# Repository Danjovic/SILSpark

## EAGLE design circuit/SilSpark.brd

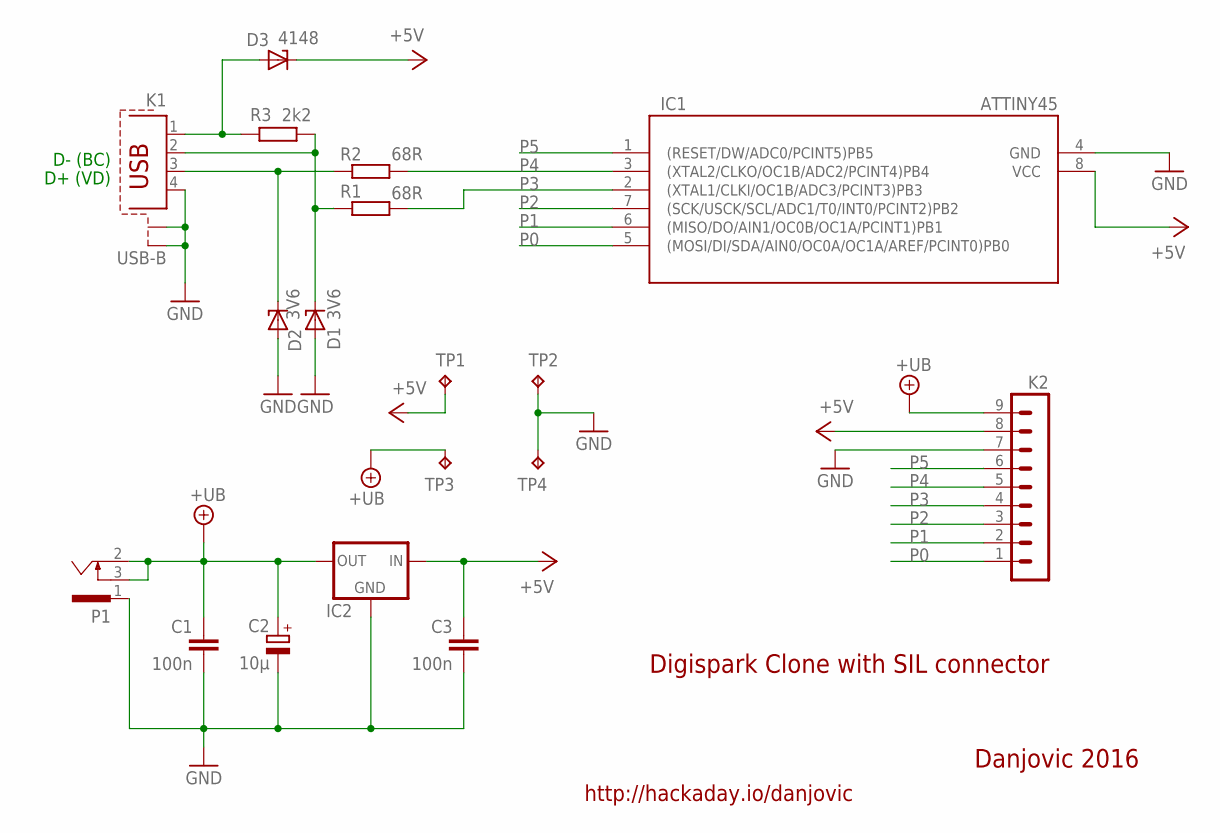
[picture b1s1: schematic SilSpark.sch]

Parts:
C1, C3: 100n; C050-025X075_LARGEPADS
C2: 10µ; E2-4_LARGEPADS
D1, D2: 3V6; ZDIO-5_LARGEPADS
D3: 4148; ZDIO-5_LARGEPADS
IC1: ATTINY45; DIL08
IC2: 78LXXFLAT; VREG-TO90FLAT
K1: USB-B; PN61729-S_LARGEPADS
K2: MA09-1W
P1: 733989-5
R1, R2: 68R; 0204/7_LARGEPADS
R3: 2k2; 0204/7_LARGEPADS
TP1, TP2, TP3, TP4: TPPAD1-13; P1-13

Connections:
+5V: C3.1, D3.C, IC1.8 (VCC), IC2.IN, K2.8, TP1.TP
+UB: C1.1, C2.+, IC2.OUT, K2.9, P1.2, P1.3, TP3.TP
D+: D2.C, K1.3, R2.2
D-: D1.C, K1.2, R1.2, R3.2
GND: C1.2, C2.-, C3.2, D1.A, D2.A, IC1.4 (GND), IC2.GND, K1.4, K1.S1, K1.S2, K2.7, P1.1, TP2.TP, TP4.TP
unnamed: D3.A, K1.1, R3.1
P0: IC1.5 ((MOSI/DI/SDA/AIN0/OC0A/OC1A/AREF/PCINT0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), K2.1
P1: IC1.6 ((MISO/DO/AIN1/OC0B/OC1A/PCINT1)PB1), K2.2
P2: IC1.7 ((SCK/USCK/SCL/ADC1/T0/INT0/PCINT2)PB2), K2.3
P3: IC1.2 ((XTAL1/CLKI/OC1B/ADC3/PCINT3)PB3), K2.4, R1.1
P4: IC1.3 ((XTAL2/CLKO/OC1B/ADC2/PCINT4)PB4), K2.5, R2.1
P5: IC1.1 ((RESET/DW/ADC0/PCINT5)PB5), K2.6

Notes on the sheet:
D- (BC)
D+ (VD)
Digispark Clone with SIL connector
Danjovic 2016
http://hackaday.io/danjovic

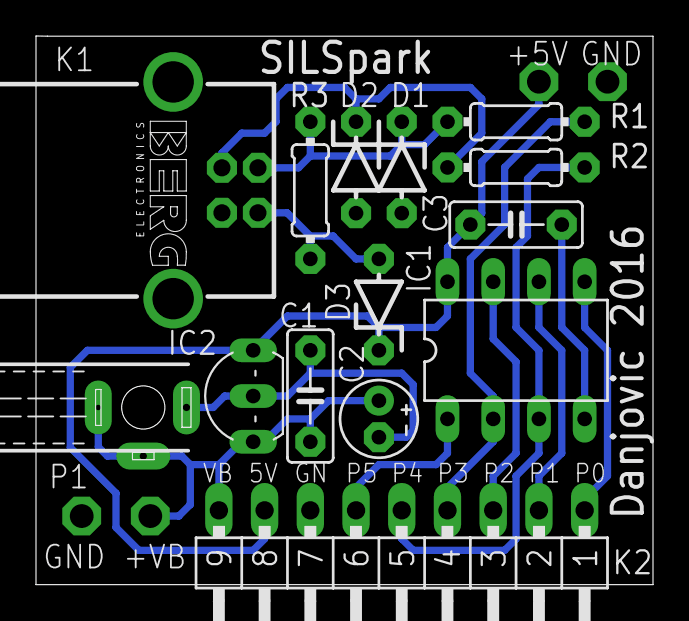
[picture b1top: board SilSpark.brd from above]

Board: 2 copper layers, 34.3 x 30.5 mm, 18 parts (0 on the bottom side), 12 nets.

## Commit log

2016-03-07 :boom::camel: Added .gitattributes & .gitignore files
2016-03-07 Basic Release
